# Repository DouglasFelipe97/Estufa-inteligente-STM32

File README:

echo "# Estufa-inteligente-STM32" >> README.md
git init
git add README.md
git commit -m "first commit"
git branch -M main
git remote add origin https://github.com/DouglasFelipe97/Estufa-inteligente-STM32.git
git push -u origin main

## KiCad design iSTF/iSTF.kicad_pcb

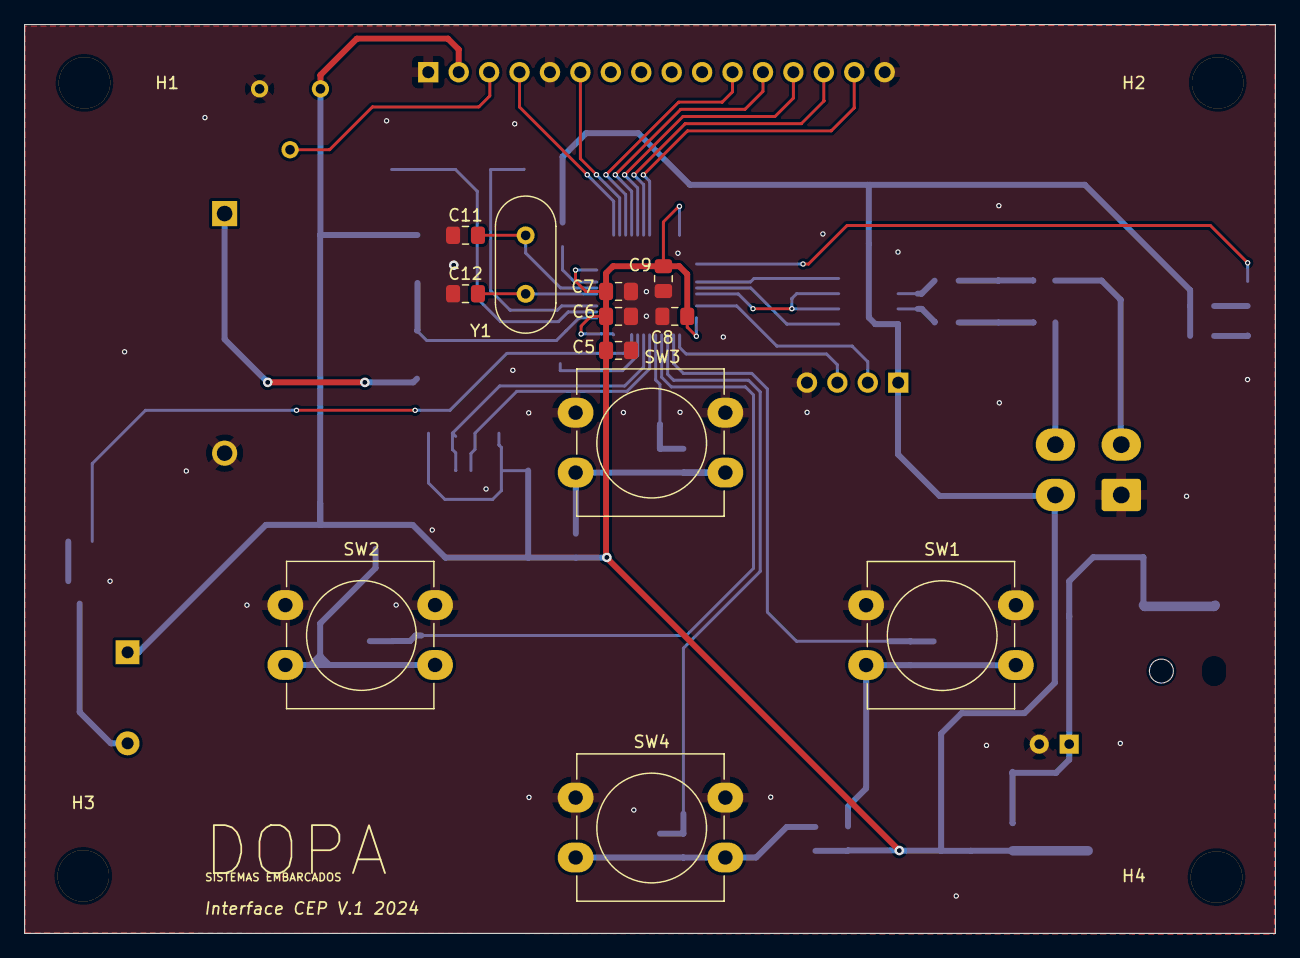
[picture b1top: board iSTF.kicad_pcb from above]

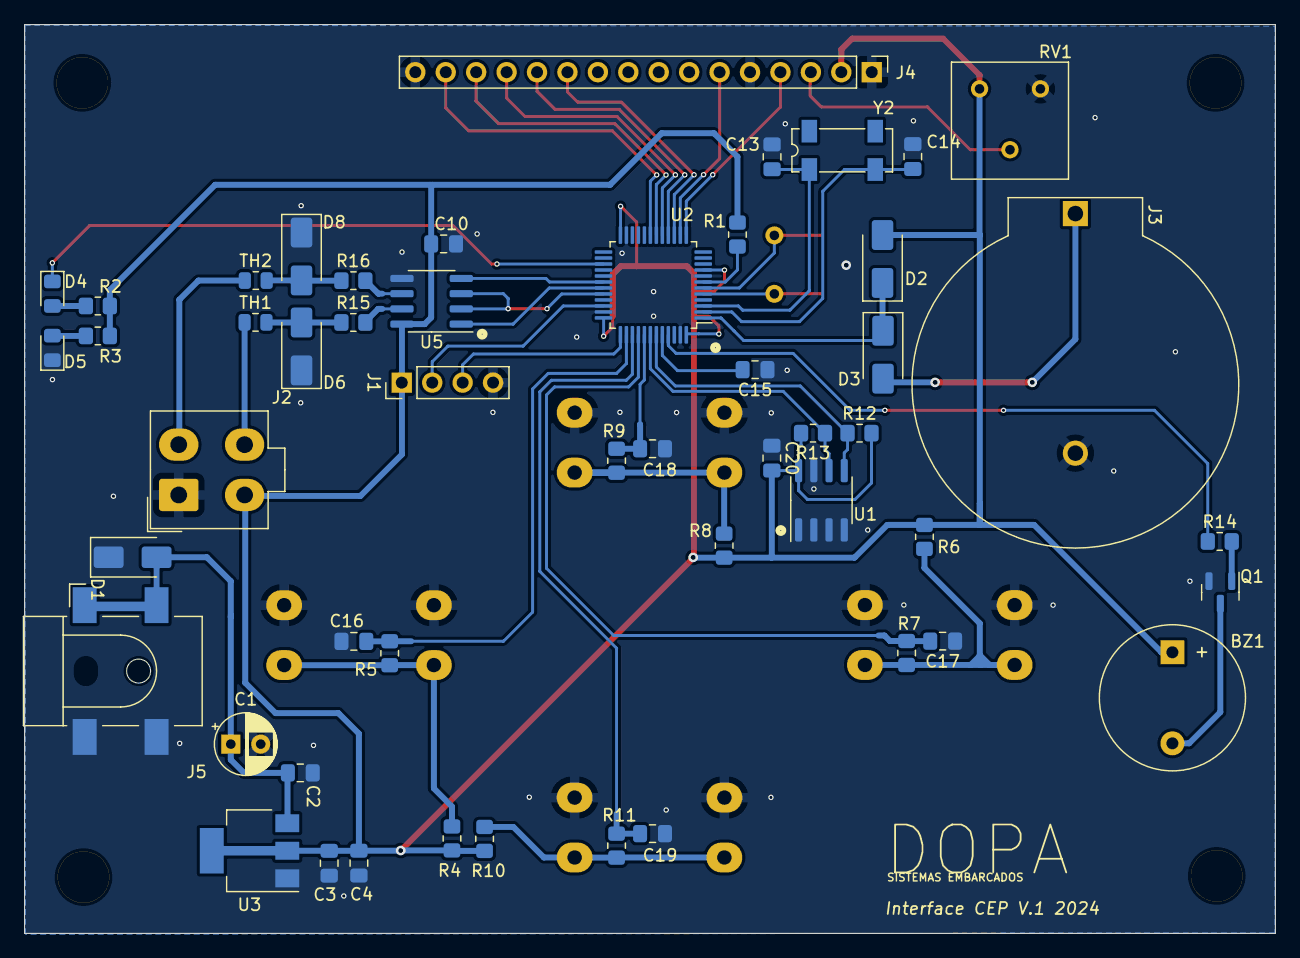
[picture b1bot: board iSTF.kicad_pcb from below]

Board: 2 copper layers, 104.4 x 75.9 mm, 67 parts (51 on the bottom side), 46 nets.

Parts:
BZ1: Buzzer; Buzzer_12x9.5RM7.6
C1: 220x16; CP_Radial_D5.0mm_P2.50mm
C2, C4, C6, C7, C8, C9, C10, C15, C16, C17, C18, C19, C20: 100nF; C_0805_2012Metric_Pad1.18x1.45mm_HandSolder
C3, C5: 10uF; C_0805_2012Metric_Pad1.18x1.45mm_HandSolder
C11, C12: 12pF; C_0805_2012Metric_Pad1.18x1.45mm_HandSolder
C13, C14: 4.3pF; C_0805_2012Metric_Pad1.18x1.45mm_HandSolder
D1: SMAJ6.5CA; D_SMA
D2, D3: US1M; D_SMA
D4, D5: LED; LED_0805_2012Metric_Pad1.15x1.40mm_HandSolder
D6, D8: SMAJ6.0CA; D_SMA
H1, H2, H3, H4: MountingHole_4.3mm_M4
J1: GRAV; PinHeader_1x04_P2.54mm_Vertical
J2: Conn_02x02_Odd_Even; Molex_Mini-Fit_Jr_5566-04A_2x02_P4.20mm_Vertical
J3: CR2032; BatteryHolder_ComfortableElectronic_CH273-2450_1x2450
J4: Conn_01x16; PinHeader_1x16_P2.54mm_Vertical
J5: Barrel_Jack_Switch_Pin3Ring; BarrelJack_CLIFF_FC681465S_SMT_Horizontal
Q1: BC817; SOT-23
R1, R4, R6, R8, R10: 10k; R_0805_2012Metric_Pad1.20x1.40mm_HandSolder
R2, R3, R14: 470R; R_0805_2012Metric_Pad1.20x1.40mm_HandSolder
R5, R7, R9, R11: 330r; R_0805_2012Metric_Pad1.20x1.40mm_HandSolder
R12, R13: 4k7; R_0805_2012Metric_Pad1.20x1.40mm_HandSolder
R15, R16: 10R; R_0805_2012Metric_Pad1.20x1.40mm_HandSolder
RV1: R_Potentiometer; Potentiometer_Bourns_3386F_Vertical
SW1: TCF; SW_PUSH-12mm_Wuerth-430476085716
SW2: TVL; SW_PUSH-12mm_Wuerth-430476085716
SW3: TCM; SW_PUSH-12mm_Wuerth-430476085716
SW4: TBX; SW_PUSH-12mm_Wuerth-430476085716
TH1, TH2: Thermistor_PTC; R_0805_2012Metric
U1: 24LC64; SOIC-8_3.9x4.9mm_P1.27mm
U2: STM32F103C8Tx; LQFP-48_7x7mm_P0.5mm
U3: LM1117MP-3.3; SOT-223-3_TabPin2
U5: SN75176AD; SOIC-8_3.9x4.9mm_P1.27mm
Y1: 25Mhz; Crystal_HC49-4H_Vertical
Y2: 32khz; Crystal_SMD_SeikoEpson_MC306-4Pin_8.0x3.2mm

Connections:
/Mcu/BLT: J4.15, U2.19 (PB1)
/Mcu/BZ1: R14.1, U2.45 (PB8)
/Mcu/D4: J4.11, U2.15 (PA5)
/Mcu/D5: J4.12, U2.16 (PA6)
/Mcu/D6: J4.13, U2.17 (PA7)
/Mcu/D7: J4.14, U2.18 (PB0)
/Mcu/EN: J4.6, U2.14 (PA4)
/Mcu/LED_ON: D4.1 (K), U2.27 (PB14)
/Mcu/NRST: R1.1, U2.7 (NRST)
/Mcu/RS: J4.4, U2.13 (PA3)
/Mcu/SWCLK: J1.3, U2.37 (PA14)
/Mcu/SWDIO: J1.2, U2.34 (PA13)
/Mcu/V0: J4.3, RV1.2
GND: C1.2, C2.1, C3.1, C4.1, C5.1, C6.1, C7.1, C8.1, C9.1, C10.1, C11.1, C12.1, C13.1, C14.1, C15.1, C16.1, C17.1, C18.1, C19.1, C20.1, D1.1 (A1), D5.1 (K), D6.1 (A1), D8.1 (A1), J1.4, J2.1, J3.2, J4.1, J4.5, J4.16, J5.2, J5.3, Q1.2 (E), RV1.3, SW1.1, SW2.1, SW3.1, SW4.1, U1.1 (A0), U1.2 (A1), U1.3 (A2), U1.4 (GND), U1.7 (WP), U2.8 (VSSA), U2.23 (VSS), U2.35 (VSS), U2.47 (VSS), U3.1 (GND), U5.5 (GND)
unnamed: BZ1.2 (+), Q1.3 (C)
unnamed: C1.1, C2.2, D1.2 (A2), J5.1, U3.3 (VI)
unnamed: D3.2 (A), J3.1
unnamed: D4.2 (A), R2.2
unnamed: D5.2 (A), R3.2
unnamed: D6.2 (A2), R15.1, TH1.2
unnamed: D8.2 (A2), R16.1, TH2.2
unnamed: J2.2, TH2.1
unnamed: J2.4, TH1.1
unnamed: Q1.1 (B), R14.2
unnamed: R4.2, R5.1, SW1.2
unnamed: R6.2, R7.1, SW2.2
unnamed: R8.2, R9.1, SW3.2
unnamed: R10.2, R11.1, SW4.2
unnamed: C15.2, U2.44 (BOOT0)
unnamed: R16.2, U5.6 (A)
unnamed: R15.2, U5.7 (B)
OSC1: C11.2, U2.6 (PD1), Y1.1
OSC2: C12.2, U2.5 (PD0), Y1.2
RSIO: U2.32 (PA11), U5.2 (~RE), U5.3 (DE)
RTC1: C13.2, U2.3 (PC14), Y2.1
RTC2: C14.2, U2.2 (PC13), Y2.2
RX: U2.31 (PA10), U5.1 (R)
SCL: R13.1, U1.6 (SCL), U2.42 (PB6)
SDA: R12.1, U1.5 (SDA), U2.43 (PB7)
TBX: C19.2, R11.2, U2.39 (PB3)
TCF: C16.2, R5.2, U2.38 (PA15)
TCM: C18.2, R9.2, U2.41 (PB5)
TVL: C17.2, R7.2, U2.40 (PB4)
TX: U2.30 (PA9), U5.4 (D)
VBAT: D2.1 (K), D3.1 (K), U2.1 (VBAT)
VDD: BZ1.1 (-), C3.2, C4.2, C5.2, C6.2, C7.2, C8.2, C9.2, C10.2, C20.2, D2.2 (A), J1.1, J2.3, J4.2, R1.2, R2.1, R3.1, R4.1, R6.1, R8.1, R10.1, R12.2, R13.2, RV1.1, U1.8 (VCC), U2.9 (VDDA), U2.24 (VDD), U2.36 (VDD), U2.48 (VDD), U3.2 (VO), U5.8 (VCC)
